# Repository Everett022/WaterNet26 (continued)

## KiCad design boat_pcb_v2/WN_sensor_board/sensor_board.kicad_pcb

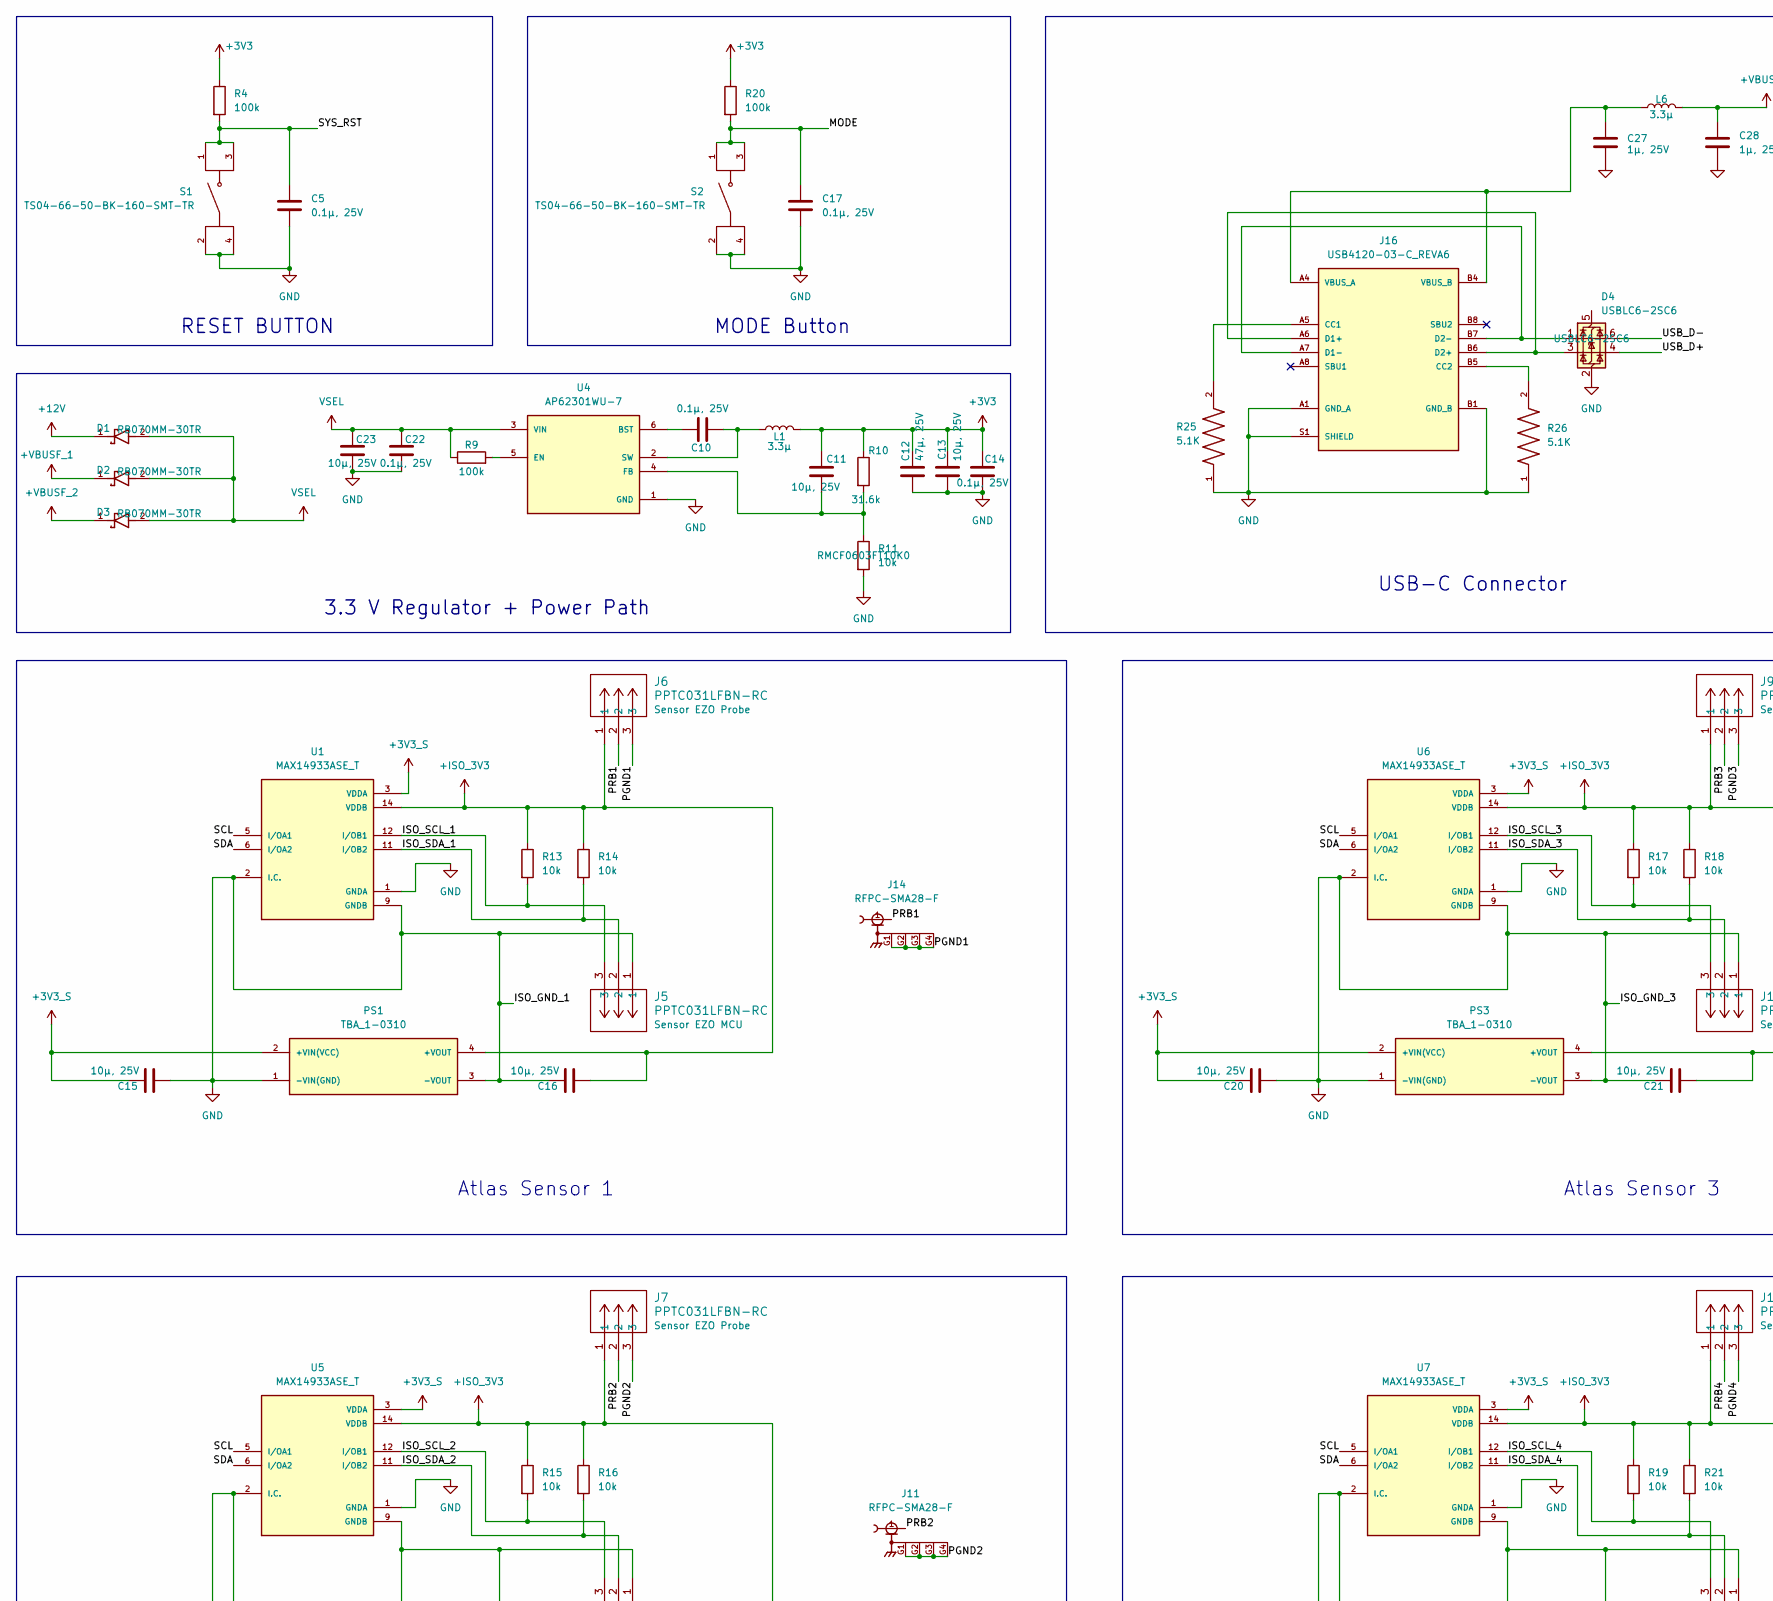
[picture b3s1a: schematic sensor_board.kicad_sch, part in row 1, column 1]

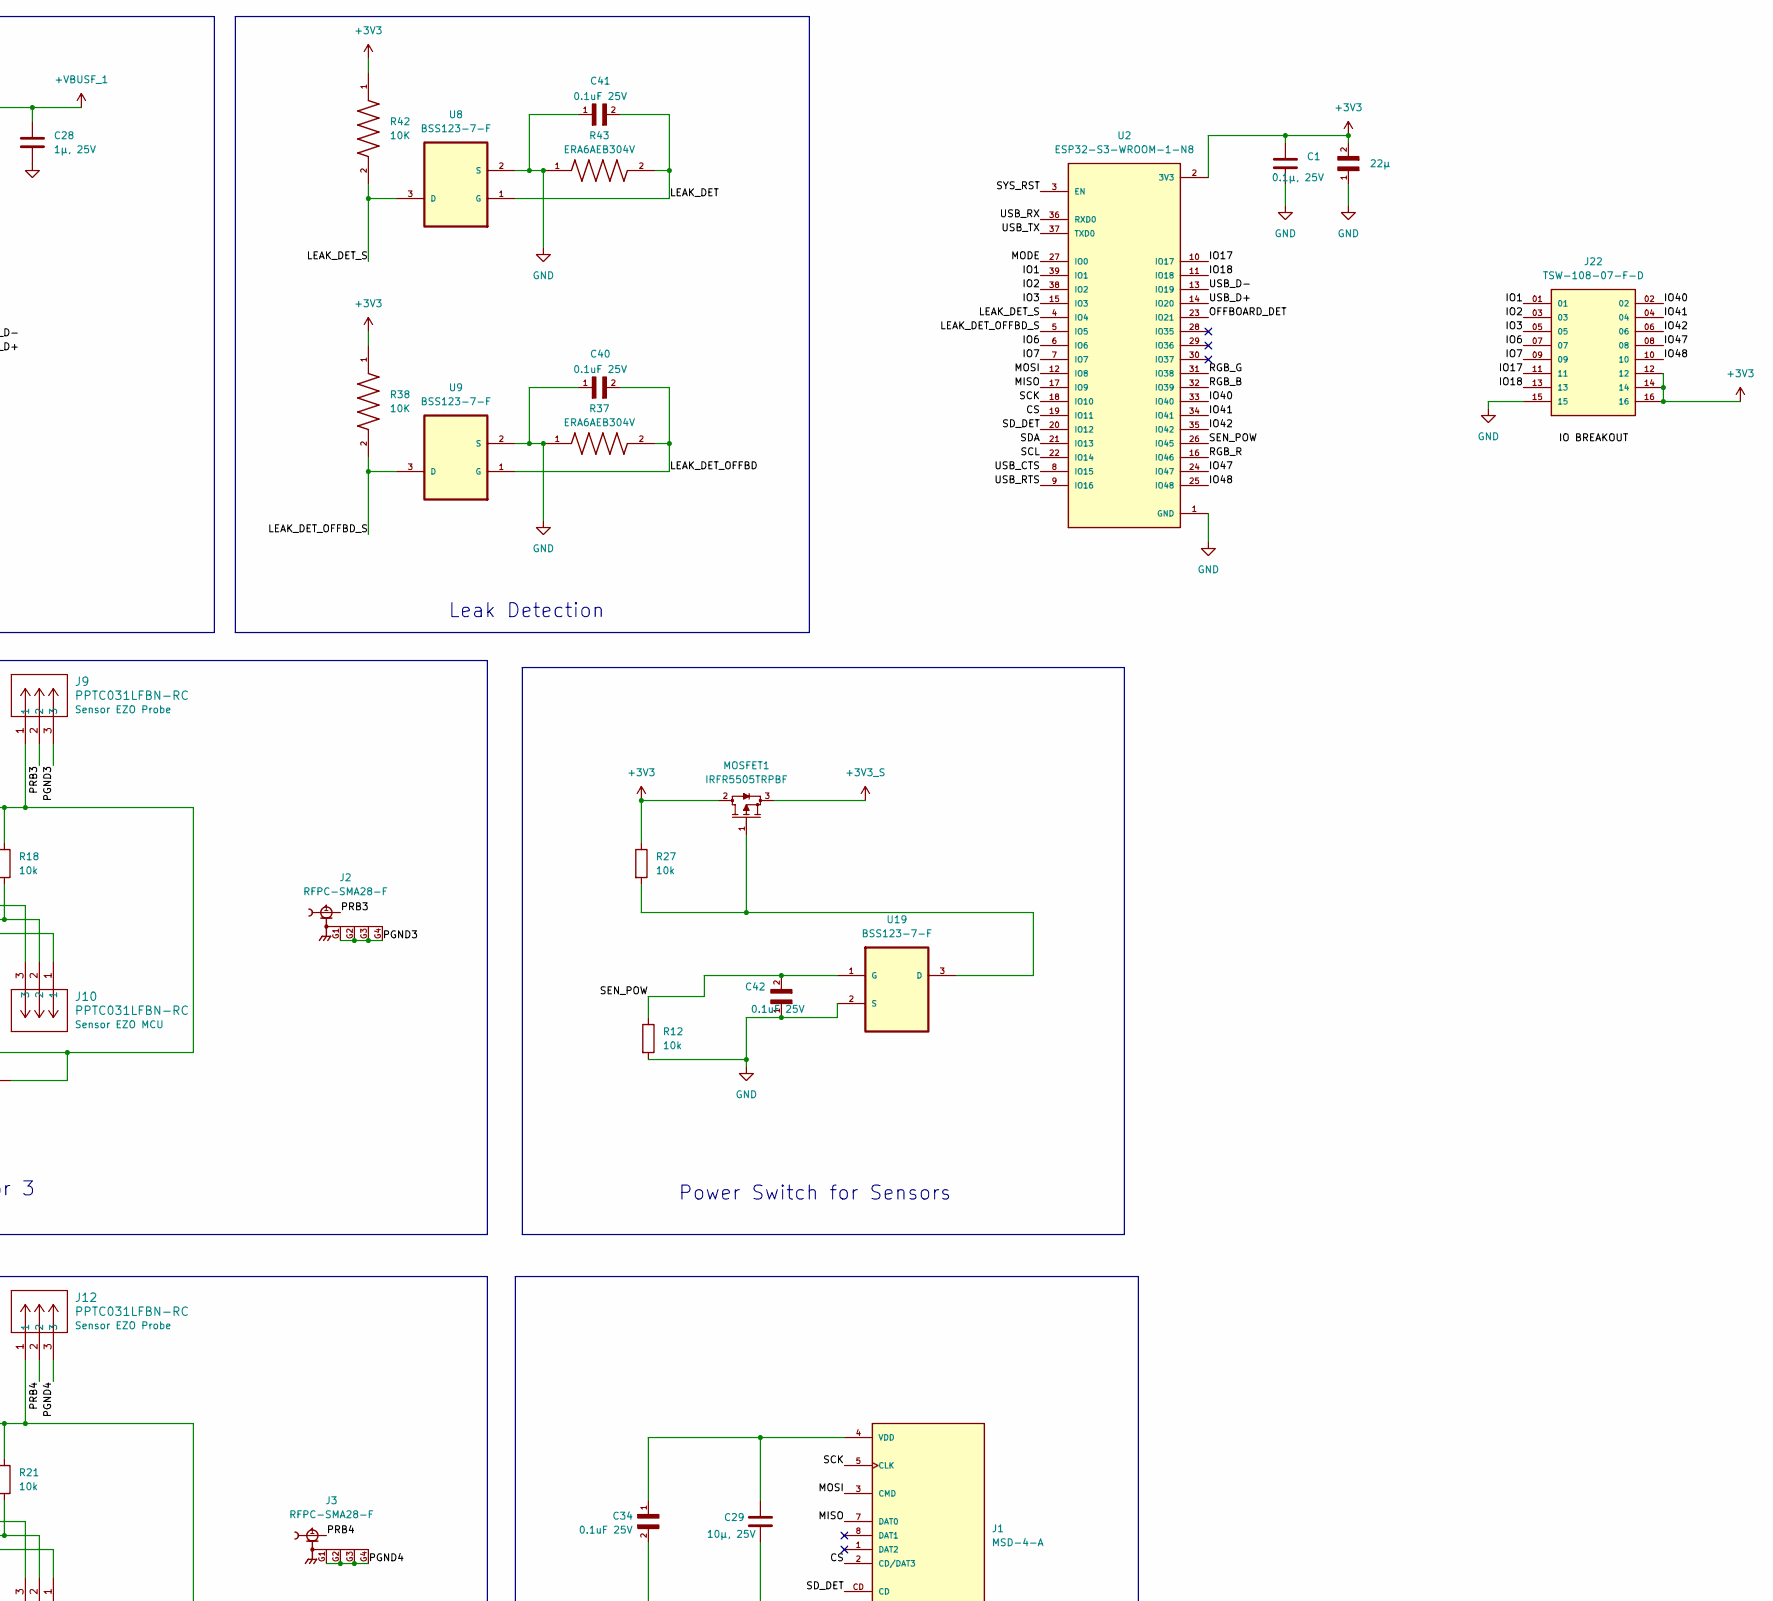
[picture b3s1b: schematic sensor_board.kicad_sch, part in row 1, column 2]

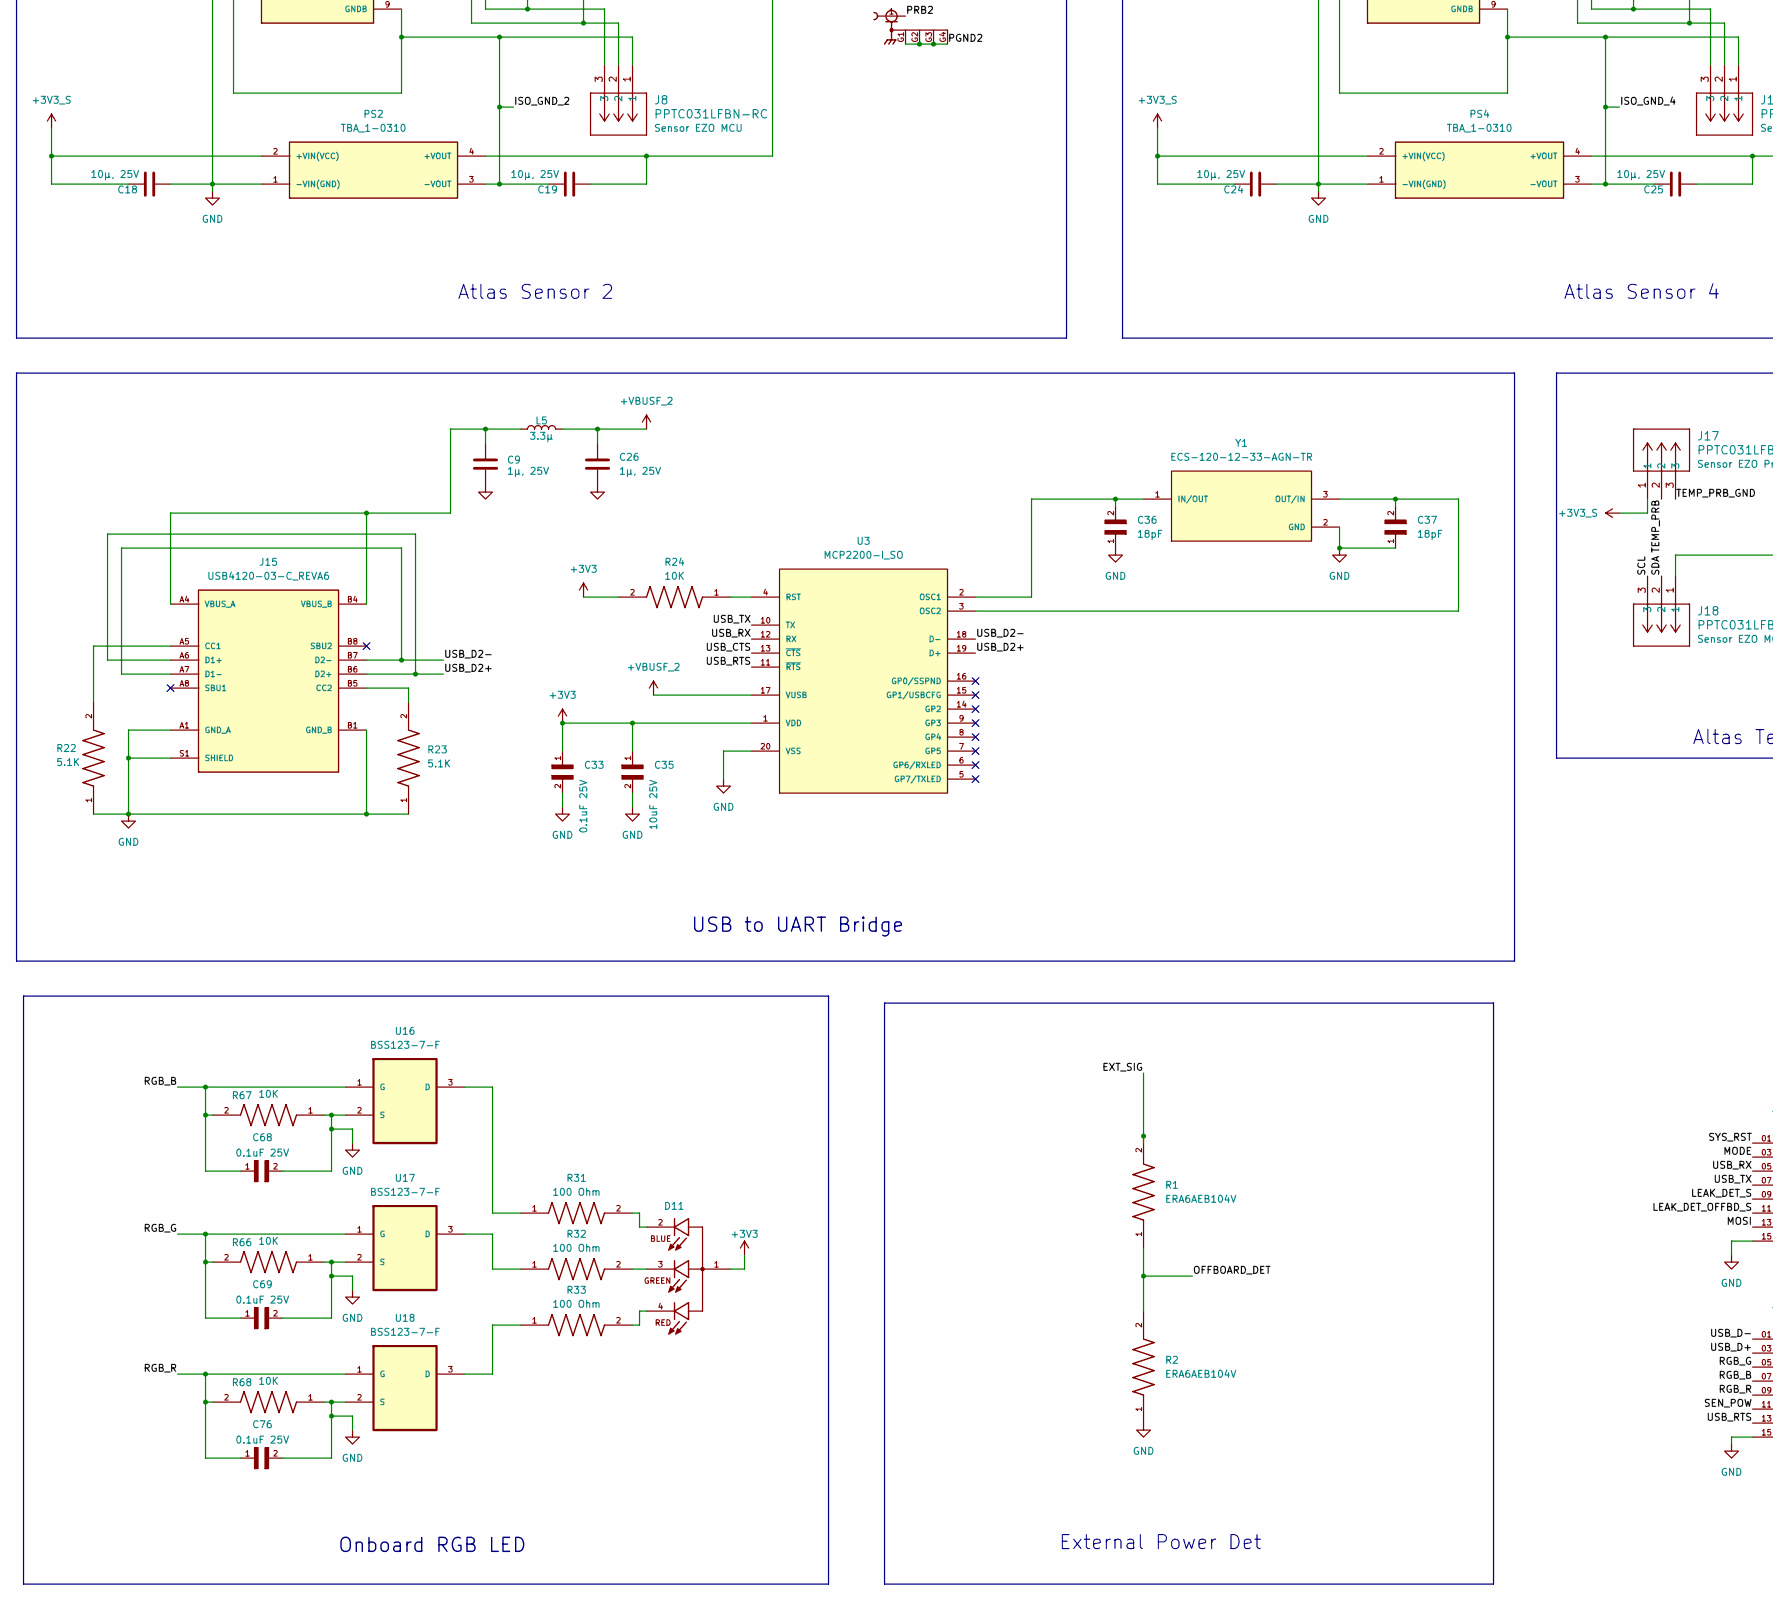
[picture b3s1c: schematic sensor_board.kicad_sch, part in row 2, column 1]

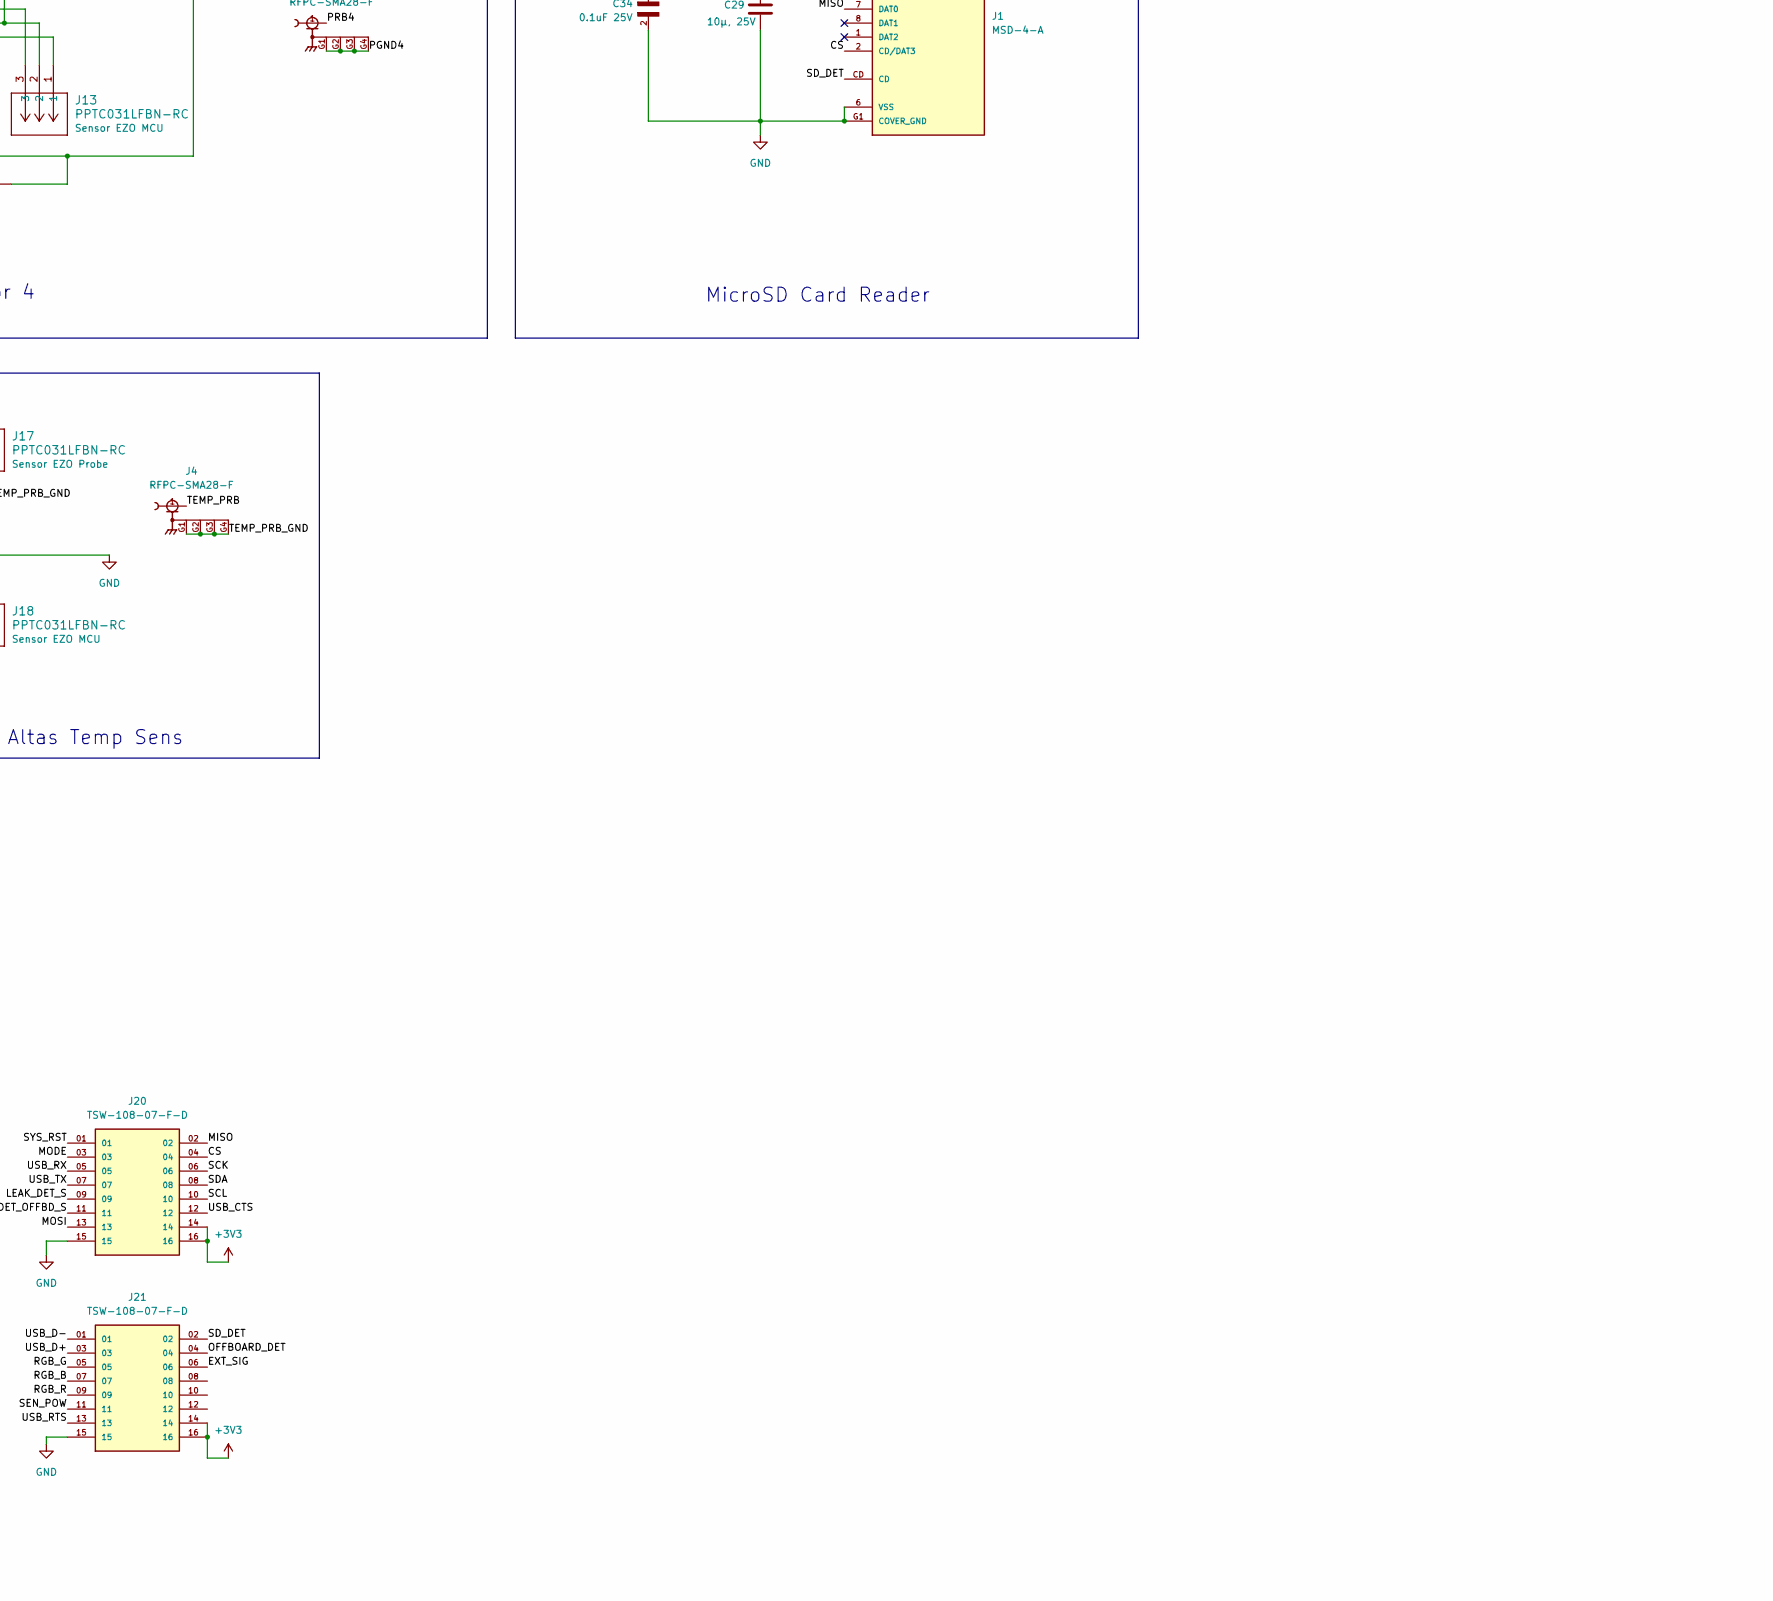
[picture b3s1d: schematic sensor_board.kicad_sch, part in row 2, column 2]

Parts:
C1, C5, C10, C14, C17, C22: 0.1µ, 25V; CAPC2012X95N
C2: 22µ; CAPC1608X105N
C9, C26, C27, C28: 1µ, 25V; CAPC2012X145N
C11, C13, C15, C16, C18, C19, C20, C21, C23, C24, C25, C29: 10µ, 25V; CAPC2012X145N
C12: 47µ, 25V; CAPC3216X180N
C33, C34, C40, C41, C42, C68, C69, C76: 0.1uF 25V; CAPC2012X95N
C35: 10uF 25V; CAPC2012X145N
C36, C37: 18pF; CAPC1608X90N
D1, D2, D3: RB070MM-30TR; SMB
D4: USBLC6-2SC6; SOT-23-6
D11: CLMVC-FKA-CL1D1L71BB7C3C3; LED_CLMVC-FKA-CL1D1L71BB7C3C3; PARTREV 14
J1: MSD-4-A; CUI_MSD-4-A; PARTREV 1.0
J2, J3, J4, J11, J14: RFPC-SMA28-F; GRADCONN_RFPC-SMA28-F; PARTREV 1.0
J5, J6, J7, J8, J9, J10, J12, J13, J17, J18: PPTC031LFBN-RC; CONN_PPTC031_SUL
J15, J16: USB4120-03-C_REVA6; GCT_USB4120-03-C_REVA6; PARTREV A6
J20, J21, J22: TSW-108-07-F-D; SAMTEC_TSW-108-07-F-D; PARTREV R
L1, L5, L6: 3.3µ; INDC1608X95N
MOSFET1: IRFR5505TRPBF; PG-TO252AA_INF; MANUFACTURER_PART_NUMBER IRFR5505TRPBF
PS1, PS2, PS3, PS4: TBA_1-0310; CONV_TBA_1-0310; PARTREV April 19, 2021
R1, R2: ERA6AEB104V; RES_ERA6AEB104V; PARTREV 3/1/2020
R4, R9, R20: 100k; RES_ERA6AEB104V
R10: 31.6k; RES_ERA6AEB3162V
R11, R12, R13, R14, R15, R16, R17, R18, R19, R21, R27: 10k; RES_ERA6AEB103V
R22, R23, R25, R26: 5.1K; RESC1508X55N
R24, R38, R42, R66, R67, R68: 10K; RES_ERA6AEB103V; PARTREV 3/1/2020
R31, R32, R33: 100 Ohm; RES_ERJ3EKF1000V; PARTREV 3/1/2020
R37, R43: ERA6AEB304V; RES_ERA6AEB304V; PARTREV 3/1/2020
S1, S2: TS04-66-50-BK-160-SMT-TR; SW_TS04-66-50-BK-160-SMT-TR; PARTREV 1.04mm
U1, U5, U6, U7: MAX14933ASE_T; SOIC127P600X175-16N
U2: ESP32-S3-WROOM-1-N8; XCVR_ESP32-S3-WROOM-1-N8
U3: MCP2200-I_SO; SOIC20; MANUFACTURER_PART_NUMBER mcp2200-i/so
U4: AP62301WU-7; SOT95P280X100-6N; PARTREV Rev. 3 - 2
U8, U9, U16, U17, U18, U19: BSS123-7-F; SOT95P240X110-3N; MPN BSS123-7-F
Y1: ECS-120-12-33-AGN-TR; XTAL_ECS-120-12-33-AGN-TR

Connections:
+3V3_S: C15.1, C18.1, C20.1, C24.1, J17.1, MOSFET1.3, PS1.2 (+VIN(VCC)), PS2.2 (+VIN(VCC)), PS3.2 (+VIN(VCC)), PS4.2 (+VIN(VCC)), U1.3 (VDDA), U5.3 (VDDA), U6.3 (VDDA), U7.3 (VDDA)
+12V: D1.1
+ISO_3V3: C16.2, C19.2, C21.2, C25.2, J6.1, J7.1, J9.1, J12.1, PS1.4 (+VOUT), PS2.4 (+VOUT), PS3.4 (+VOUT), PS4.4 (+VOUT), R13.1, R14.1, R15.1, R16.1, R17.1, R18.1, R19.1, R21.1, U1.14 (VDDB), U5.14 (VDDB), U6.14 (VDDB), U7.14 (VDDB)
+VBUSF_1: C28.1, D2.1, L6.2
+VBUSF_2: C26.1, D3.1, L5.2, U3.17 (VUSB)
/CS: J1.2 (CD/DAT3), J20.04, U2.19 (IO11)
/IO1: J22.01, U2.39 (IO1)
/IO2: J22.03, U2.38 (IO2)
/IO3: J22.05, U2.15 (IO3)
/IO6: J22.07, U2.6 (IO6)
/IO7: J22.09, U2.7 (IO7)
/IO17: J22.11, U2.10 (IO17)
/IO18: J22.13, U2.11 (IO18)
/IO40: J22.02, U2.33 (IO40)
/IO41: J22.04, U2.34 (IO41)
/IO42: J22.06, U2.35 (IO42)
/IO47: J22.08, U2.24 (IO47)
/IO48: J22.10, U2.25 (IO48)
/ISO_SCL_1: J5.3, R13.2, U1.12 (I/OB1)
/ISO_SCL_2: J8.3, R15.2, U5.12 (I/OB1)
/ISO_SCL_3: J10.3, R17.2, U6.12 (I/OB1)
/ISO_SCL_4: J13.3, R19.2, U7.12 (I/OB1)
/ISO_SDA_1: J5.2, R14.2, U1.11 (I/OB2)
/ISO_SDA_2: J8.2, R16.2, U5.11 (I/OB2)
/ISO_SDA_3: J10.2, R18.2, U6.11 (I/OB2)
/ISO_SDA_4: J13.2, R21.2, U7.11 (I/OB2)
/LEAK_DET: C41.2, R43.2, U8.1 (G)
/LEAK_DET_OFFBD: C40.2, R37.2, U9.1 (G)
/LEAK_DET_OFFBD_S: J20.11, R38.2, U2.5 (IO5), U9.3 (D)
/LEAK_DET_S: J20.09, R42.2, U2.4 (IO4), U8.3 (D)
/MISO: J1.7 (DAT0), J20.02, U2.17 (IO9)
/MOSI: J1.3 (CMD), J20.13, U2.12 (IO8)
/PGND1: J6.3, J14.G1, J14.G2, J14.G3, J14.G4
/PGND2: J7.3, J11.G1, J11.G2, J11.G3, J11.G4
/PGND3: J2.G1, J2.G2, J2.G3, J2.G4, J9.3
/PGND4: J3.G1, J3.G2, J3.G3, J3.G4, J12.3
/PRB1: J6.2, J14.1
/PRB2: J7.2, J11.1
/PRB3: J2.1, J9.2
/PRB4: J3.1, J12.2
/RGB_B: C68.1, J21.07, R67.2, U2.32 (IO39), U16.1 (G)
/RGB_G: C69.1, J21.05, R66.2, U2.31 (IO38), U17.1 (G)
/RGB_R: C76.1, J21.09, R68.2, U2.16 (IO46), U18.1 (G)
/SCK: J1.5 (CLK), J20.06, U2.18 (IO10)
/SCL: J18.3, J20.10, U1.5 (I/OA1), U2.22 (IO14), U5.5 (I/OA1), U6.5 (I/OA1), U7.5 (I/OA1)
/SDA: J18.2, J20.08, U1.6 (I/OA2), U2.21 (IO13), U5.6 (I/OA2), U6.6 (I/OA2), U7.6 (I/OA2)
/SD_DET: J1.CD, J21.02, U2.20 (IO12)
/SEN_POW: C42.2, J21.11, R12.1, U2.26 (IO45), U19.1 (G)
/SYS_RST: C5.1, J20.01, R4.2, S1.1, S1.3, U2.3 (EN); also elsewhere on the board
/TEMP_PRB: J4.1, J17.2
/TEMP_PRB_GND: J4.G1, J4.G2, J4.G3, J4.G4, J17.3
/USB_CTS: J20.12, U2.8 (IO15), U3.13 (~CTS)
/USB_D2+: J15.A6 (D1+), J15.B6 (D2+), U3.19 (D+)
/USB_D2-: J15.A7 (D1-), J15.B7 (D2-), U3.18 (D-)
/USB_D+: D4.4 (I/O2), J21.03, U2.14 (IO20)
/USB_D-: D4.6 (I/O1), J21.01, U2.13 (IO19)
/USB_RTS: J21.13, U2.9 (IO16), U3.11 (~RTS)
/USB_RX: J20.05, U2.36 (RXD0), U3.12 (RX)
/USB_TX: J20.07, U2.37 (TXD0), U3.10 (TX)
GND: C1.2, C2.1, C5.2, C9.2, C12.2, C13.2, C14.2, C15.2, C16.1, C17.2, C18.2, C19.1, C20.2, C21.1, C22.2, C23.2, C24.2, C25.1, C26.2, C27.2, C28.2, C29.1, C33.2, C34.2, C35.2, C36.1, C37.1, C40.1, C41.1, C42.1, C68.2, C69.2, C76.2, D4.2 (GND), J1.6 (VSS), J1.G1 (COVER_GND), J1.G2 (COVER_GND), J1.G3 (COVER_GND), J1.G4 (COVER_GND), J5.1, J8.1, J10.1, J13.1, J15.A1 (GND_A), J15.A12 (GND_A), J15.B1 (GND_B), J15.B12 (GND_B), J15.S1 (SHIELD), J15.S2 (SHIELD), J15.S3 (SHIELD), J15.S4 (SHIELD), J16.A1 (GND_A), J16.A12 (GND_A), J16.B1 (GND_B), J16.B12 (GND_B), J16.S1 (SHIELD), J16.S2 (SHIELD), J16.S3 (SHIELD), J16.S4 (SHIELD), J18.1, J20.15, J21.15, J22.15, PS1.1 (-VIN(GND)), PS1.3 (-VOUT), PS2.1 (-VIN(GND)), PS2.3 (-VOUT), PS3.1 (-VIN(GND)), PS3.3 (-VOUT), PS4.1 (-VIN(GND)), PS4.3 (-VOUT), R2.1, R11.2, R12.2, R22.1, R23.1, R25.1, R26.1, R37.1, R43.1, R66.1, R67.1, R68.1, S1.2, S1.4, S2.2, S2.4, U1.1 (GNDA), U1.2 (I.C.), U1.7 (GNDA), U1.8 (I.C.), U1.9 (GNDB), U1.10 (I.C.), U1.15 (I.C.), U1.16 (GNDB), U2.1 (GND), U2.40 (GND), U2.41_1 (GND), U2.41_2 (GND), U2.41_3 (GND), U2.41_4 (GND), U2.41_5 (GND), U2.41_6 (GND), U2.41_7 (GND), U2.41_8 (GND), U2.41_9 (GND), U3.20 (VSS), U4.1 (GND), U5.1 (GNDA), U5.2 (I.C.), U5.7 (GNDA), U5.8 (I.C.), U5.9 (GNDB), U5.10 (I.C.), U5.15 (I.C.), U5.16 (GNDB), U6.1 (GNDA), U6.2 (I.C.), U6.7 (GNDA), U6.8 (I.C.), U6.9 (GNDB), U6.10 (I.C.), U6.15 (I.C.), U6.16 (GNDB), U7.1 (GNDA), U7.2 (I.C.), U7.7 (GNDA), U7.8 (I.C.), U7.9 (GNDB), U7.10 (I.C.), U7.15 (I.C.), U7.16 (GNDB), U8.2 (S), U9.2 (S), U16.2 (S), U17.2 (S), U18.2 (S), U19.2 (S), Y1.2 (GND), Y1.4 (GND); also elsewhere on the board
unnamed: D11.2, R31.2
unnamed: D11.3, R32.2
unnamed: D11.4, R33.2
unnamed: C29.2, C34.1, J1.4 (VDD)
unnamed: J15.A5 (CC1), R22.2
unnamed: J15.B5 (CC2), R23.2
unnamed: J16.A5 (CC1), R25.2
unnamed: J16.B5 (CC2), R26.2
unnamed: D4.3 (I/O2), J16.A6 (D1+), J16.B6 (D2+)
unnamed: D4.1 (I/O1), J16.A7 (D1-), J16.B7 (D2-)
unnamed: C36.2, U3.2 (OSC1), Y1.1 (IN/OUT)
unnamed: C37.2, U3.3 (OSC2), Y1.3 (OUT/IN)
unnamed: R24.1, U3.4 (RST)
unnamed: C10.1, U4.6 (BST)
unnamed: R9.2, U4.5 (EN)
unnamed: C11.2, R10.2, R11.1, U4.4 (FB)
unnamed: C10.2, L1.1, U4.2 (SW)
unnamed: R31.1, U16.3 (D)
unnamed: R32.1, U17.3 (D)
unnamed: R33.1, U18.3 (D)
unnamed: MOSFET1.1, R27.2, U19.3 (D)
VSEL: C22.1, C23.1, D1.2, D2.2, D3.2, R9.1, U4.3 (VIN)

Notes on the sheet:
USB-C Connector
Atlas Sensor 1
Leak Detection
MODE Button
RESET BUTTON
Onboard RGB LED
MicroSD Card Reader
External Power Det
Atlas Sensor 4
Atlas Sensor 3
Altas Temp Sens
USB to UART Bridge
Power Switch for Sensors
3.3 V Regulator + Power Path
Atlas Sensor 2

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
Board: 4 copper layers, 120 parts (12 on the bottom side), 86 nets, no tracks yet.

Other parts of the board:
C6: 1µF; CAPC2012X145N
R1#2: ERA6AEB104V; RES_ERA6AEB104V
R5: 10k; RES_ERA6AEB103V

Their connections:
/SYS_RST: C6.1, R5.2; also elsewhere on the board
GND: C6.2; also elsewhere on the board

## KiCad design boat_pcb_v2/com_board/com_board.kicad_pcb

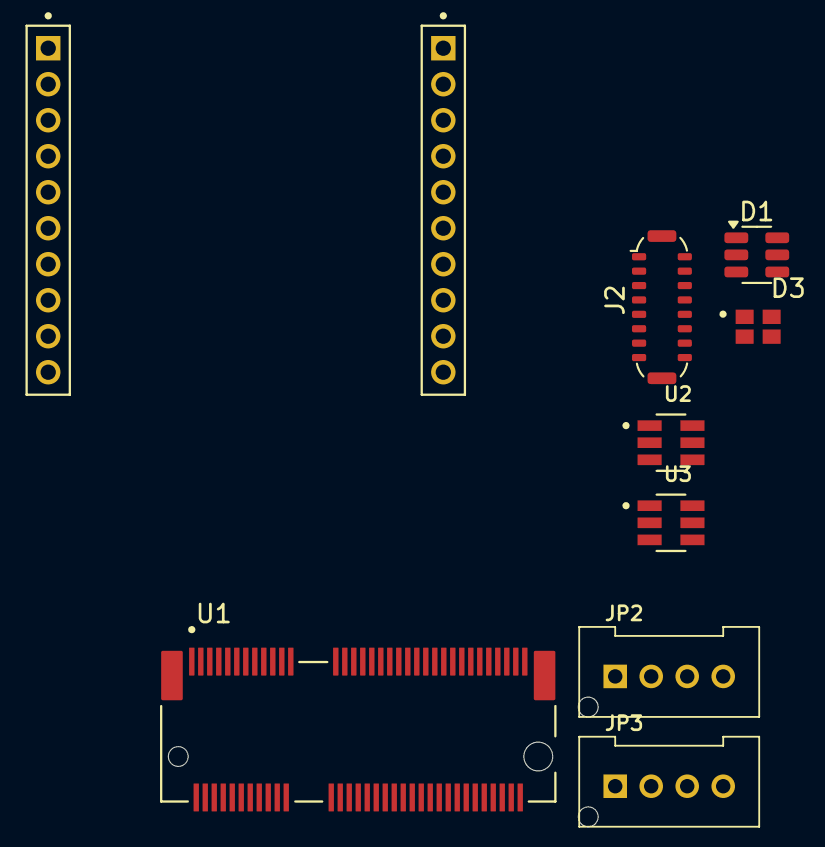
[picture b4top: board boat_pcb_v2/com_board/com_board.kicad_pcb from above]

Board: 2 copper layers, 9 parts (0 on the bottom side), 14 nets, no tracks yet.

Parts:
D1: USBLC6-2SC6; SOT-23-6
D3: CLMVC-FKA-CL1D1L71BB7C3C3; LED_CLMVC-FKA-CL1D1L71BB7C3C3
J2: USB_C_Receptacle_USB2.0_16P; USB_C_Plug_ShenzhenJingTuoJin_918-118A2021Y40002_Vertical
J7: XBP9B-DMUTB002; SULLINS_NPPN101BFCN-RC
JP2, JP3: B04B-PASK-1
U1: Particle_B404X; b404x
U2, U3: AP62301WU-7; SOT95P280X100-6N

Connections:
+3V3: J7.1 (VCC), JP2.2, JP3.2, U1.10 (3V3), U1.12 (3V3)
+3V8: U1.2 (VCC), U1.4 (VCC), U1.6 (VCC), U1.8 (VCC)
+VBUS: D1.5 (VBUS), J2.A4 (VBUS), J2.A9 (VBUS), J2.B4 (VBUS), J2.B9 (VBUS)
/RESET: J7.5 (RESET), U1.34 (RESET)
/RX: J7.2 (DOUT/DIO13), U1.38 (RX)
/SCL: JP2.4, JP3.4, U1.20 (SCL)
/SDA: JP2.3, JP3.3, U1.22 (SDA)
/TX: J7.3 (DIN/CONFIG/DIO14), U1.36 (TX)
/USB_D+: D1.3 (I/O2), J2.A6 (D+), J2.B6 (D+)
/USB_D+_S: D1.4 (I/O2), U1.11 (USB_D+)
/USB_D-: D1.1 (I/O1), J2.A7 (D-), J2.B7 (D-)
/USB_D-_S: D1.6 (I/O1), U1.13 (USB_D-)
GND: D1.2 (GND), J2.A1 (GND), J2.A12 (GND), J2.B1 (GND), J2.B12 (GND), J2.S1 (SHIELD), J7.10 (GND), JP2.1, JP3.1, U1.1 (GND), U1.3 (GND), U1.5 (GND), U1.7 (GND), U1.9 (GND), U1.15 (GND), U1.21 (GND), U1.39 (AGND), U1.49 (AGND), U1.56 (GND), U1.S1 (SHIELD), U1.S2 (SHIELD), U2.1 (GND), U3.1 (GND)
VSEL: U2.3 (VIN), U3.3 (VIN)

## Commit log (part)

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2026-04-20 com board schematic and BOM complete
2026-04-20 Changed folders for symbols and footprints
2026-05-30 Add submodule
2026-05-30 Power Board Initial Commit
2026-05-30 Changes to file naming and sensor schematic
2026-06-03 Updated submodule
2026-06-06 Added WaterNet26_Library Submodule properly
2026-06-06 Added submodule files
2026-06-10 Add gitignore for backup folder. Update submodule for library gitignore
2026-06-10 Update gitignore to not store backups in new folder structure
2026-06-10 Update WaterNetPowerBoard to reference fixed library submodule
2026-06-14 Changes made to footprints and symbols in existing schematics
2026-06-15 Finished Sensor Board
2026-06-19 Began Jetson board
2026-06-20 Adafruit breakout, USBC, Regulator
